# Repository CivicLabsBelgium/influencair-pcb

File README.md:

# influencair-pcb

A most simple version we could came up with for the Sensor.Community sensor.

(!! be carefull PCB Qty is still 250 !!)

### BOM (bill of material)
- 1 x [NodeMcu V3 Lolin](https://www.aliexpress.com/item/LoLin-V3-NodeMcu-Lua-CH340G-ESP8266-WIFI-Internet-Development-Board-Module-Free-Shipping/32768126855.html)
- 1 x [DHT22](https://www.aliexpress.com/item/DHT22-AM2302-Digital-Temperature-and-Humidity-Sensor-Replace-SHT11-SHT15/32651317108.html)
- 1 x [SDS011 PM sensor + included white cable](https://www.aliexpress.com/item/Nova-PM-sensor-SDS011-High-precision-laser-pm2-5-air-quality-detection-sensor-module-Super-dust/32606349048.html) 
- 1 x [JST 5pin angled connector](https://www.aliexpress.com/item/100Pcs-2-54Mm-Spacing-series-Right-Angle-Bend-the-foot-Jst-Xh-Connector-Pin-Header-White/32819782475.html)
- 3 x [6mm nylon standoff](https://www.aliexpress.com/item/100Pcs-Spacer-Standoff-Black-PA66-M3-Female-x-M3-Female-Hex-Threaded-Nylon-Standoff-Threaded-Spacer/32800902427.html) 
- 6 x [5mm nylon screws](https://www.aliexpress.com/item/100Pcs-Lot-M3-Screws-Black-Nylon-Screws-5-10mm-Optional-Hex-Column-Standoff-Spacer-Phillips-Screw/32839259882.html)
- 1 x **optional** 10K Ohm resistor
- 2 x 90° angle pvc pipe 75mm
- 1 x flexible tube 8mm

### Info
- Designed with EagleCAD
- Based on [Sensor.Community](https://sensor.community) sensor
- Inspiration from https://github.com/Naesstrom/airrohr-PCB
- [Gerber files](https://github.com/CivicLabsBelgium/influencair-pcb/raw/master/influencair_2018-05-10.zip) made for seeedstudio fusion service. **Standard pcb settings** except color white, refects more heat then a black one.

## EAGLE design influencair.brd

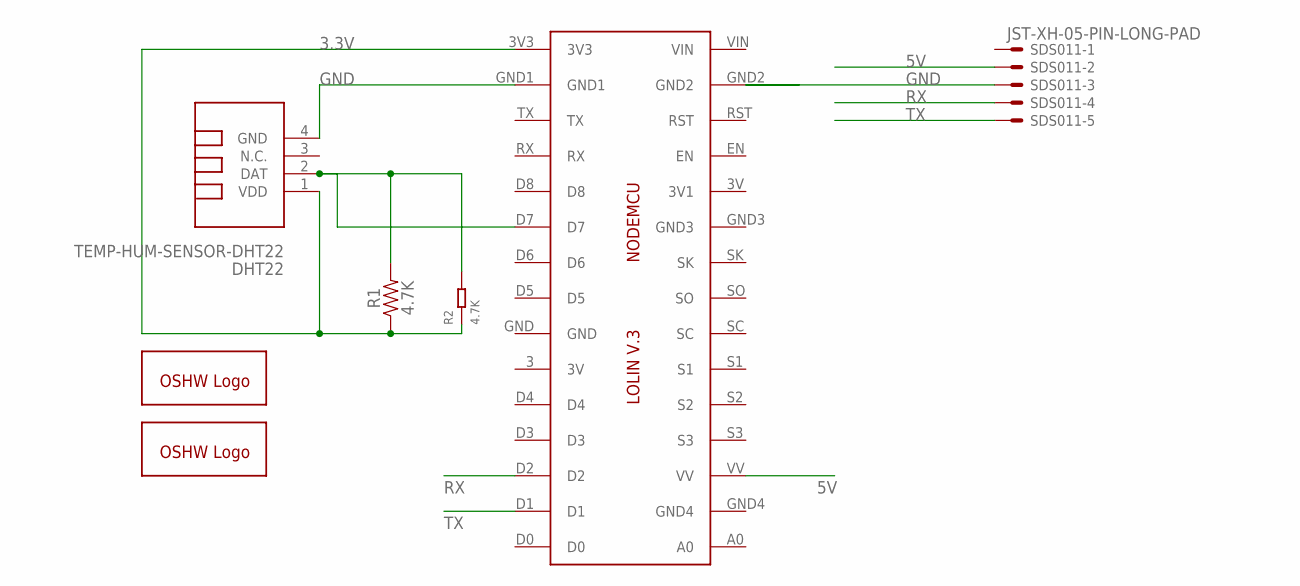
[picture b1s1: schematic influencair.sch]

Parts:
DHT22: TEMP-HUM-SENSOR-DHT22
GOLD_ORB_SM1, GOLD_ORB_SM2: OSHWLOGOLOGO8MM; OSHW_8MM
IC1: LOLINV3
R1: 4.7K; AXIAL-0.3
R2: 4.7K; R0805
SDS011: JST-XH-05-PIN-LONG-PAD; JST-XH-05-PACKAGE-LONG-PAD

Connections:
3.3V: DHT22.1 (VDD), IC1.3V3, R1.P$1 (1), R2.1
5V: IC1.VV, SDS011.2
GND: DHT22.4 (GND), IC1.GND1, SDS011.3
unnamed: DHT22.2 (DAT), IC1.D7, R1.P$2 (2), R2.2
RX: IC1.D2, SDS011.4
TX: IC1.D1, SDS011.5

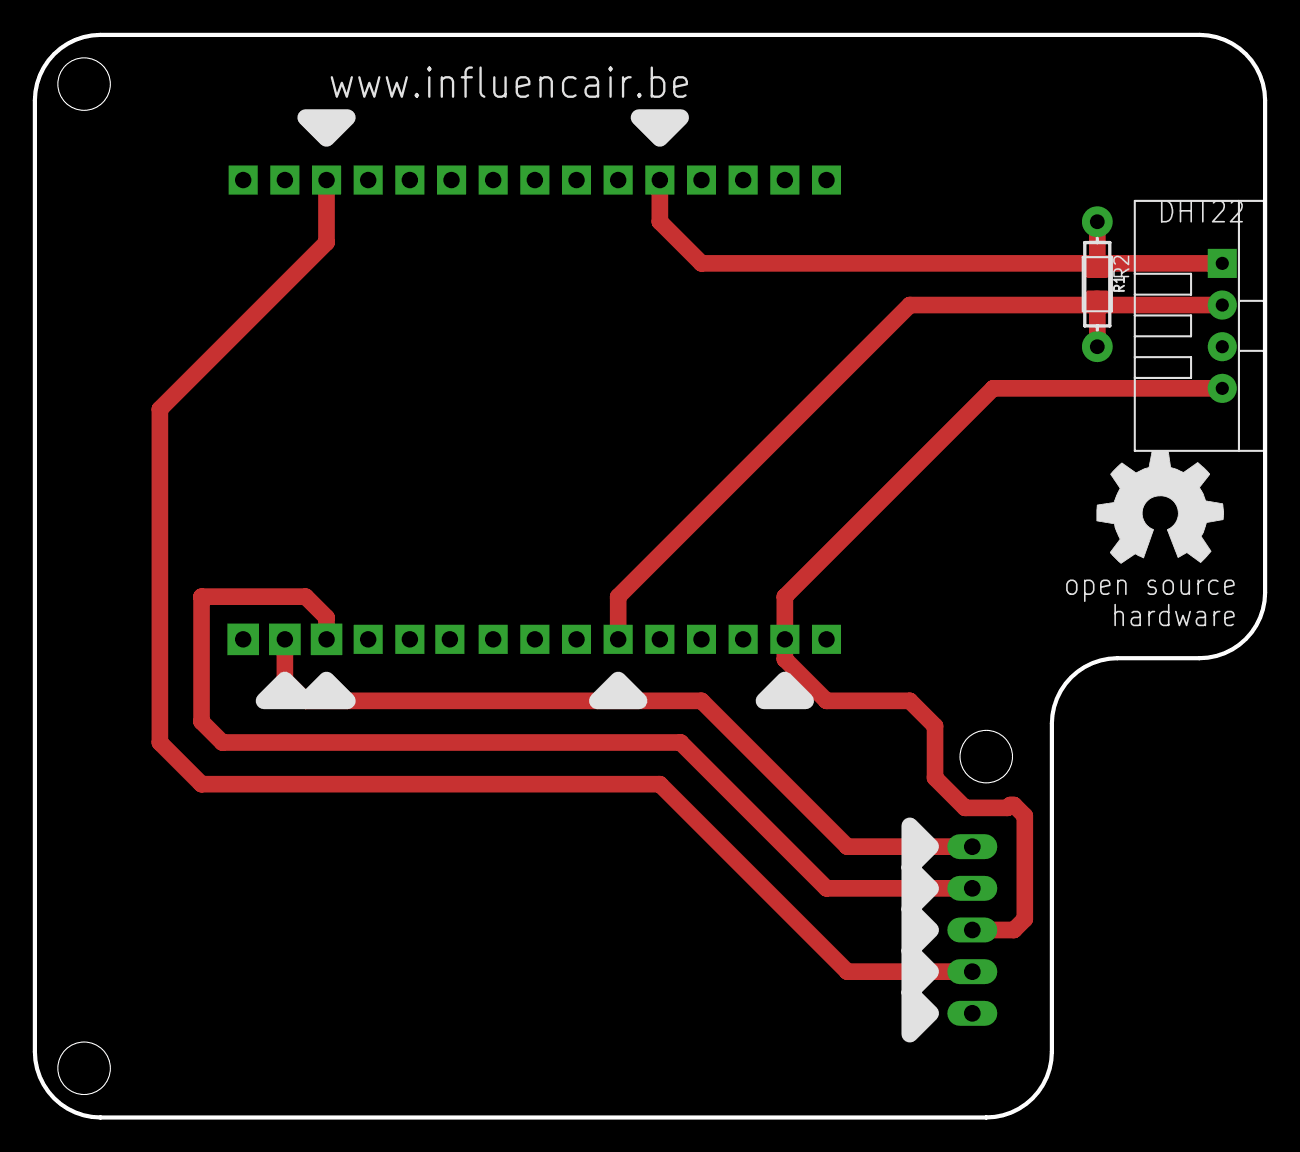
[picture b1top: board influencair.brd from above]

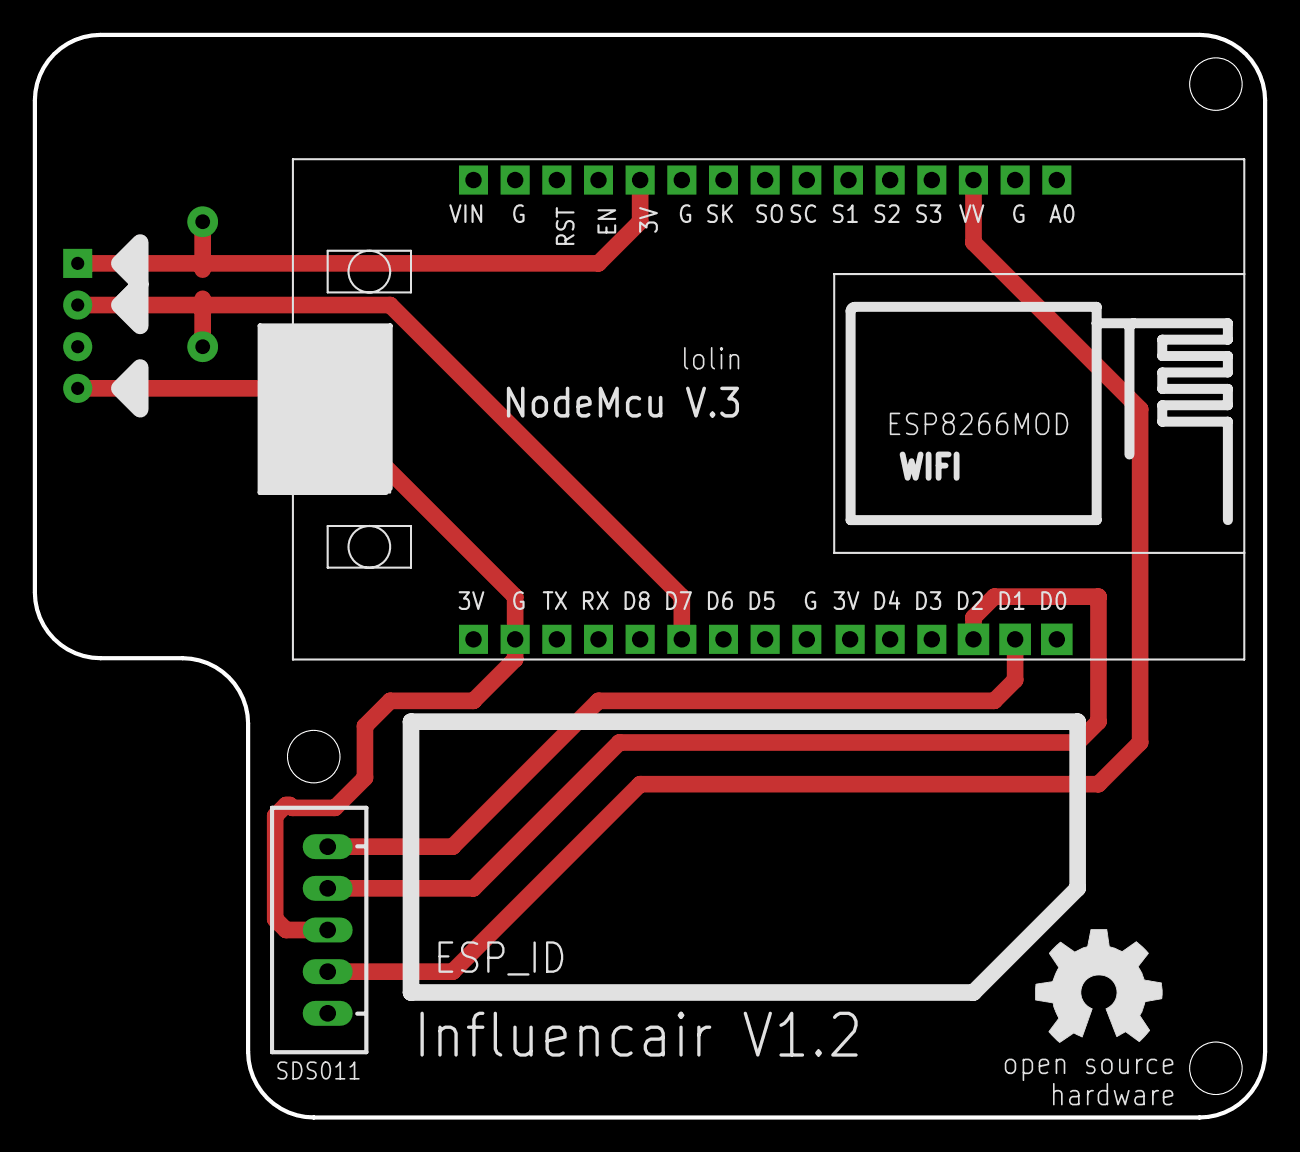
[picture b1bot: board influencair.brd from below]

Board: 2 copper layers, 75.0 x 66.0 mm, 7 parts (3 on the bottom side), 6 nets.

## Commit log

2018-06-01 Source files
2018-06-01 adding info
2018-06-04 Create folder
2018-06-04 add image
2018-06-04 new info readme
2018-06-05 add pcb order via seeedstudio
2018-06-05 Update readme
    added links to aliexpress
2023-09-11 Update README.md
    Change the name to Sensor.Community

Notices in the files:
parts and their libraries:
diy-modules: Released under the Creative Commons Attribution 4.0 International License: http://creativecommons.org/licenses/by/4.0
SparkFun-Resistors: Licensing: Creative Commons ShareAlike 4.0 International - https://creativecommons.org/licenses/by-sa/4.0
